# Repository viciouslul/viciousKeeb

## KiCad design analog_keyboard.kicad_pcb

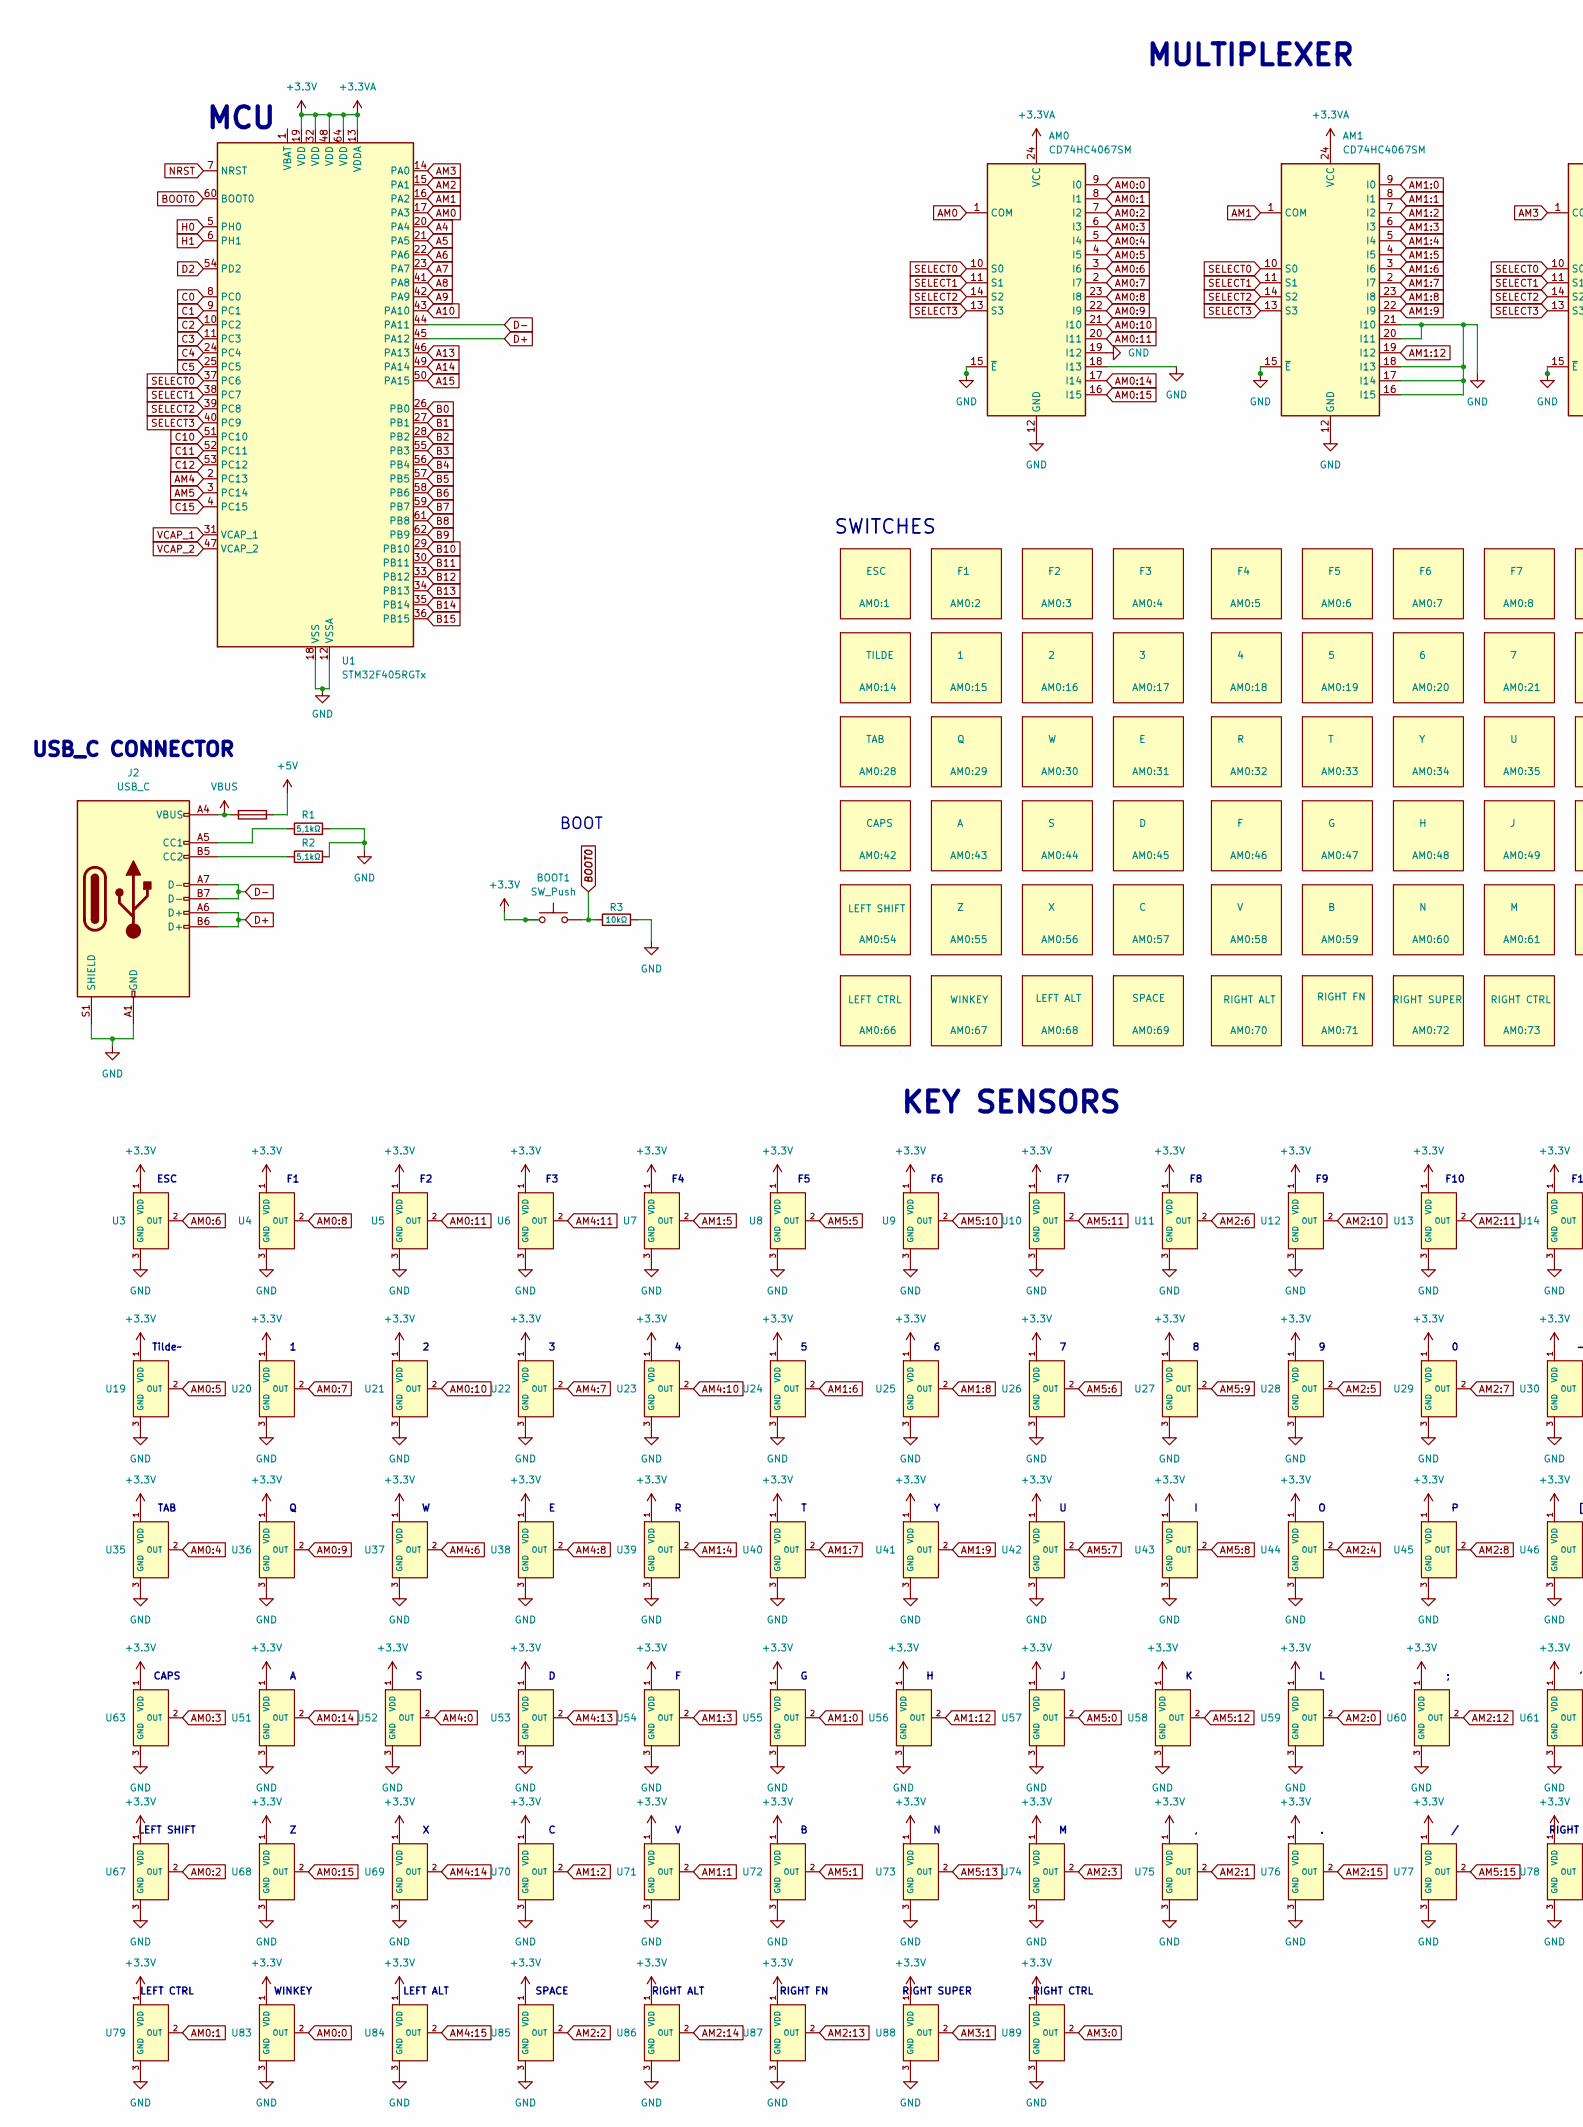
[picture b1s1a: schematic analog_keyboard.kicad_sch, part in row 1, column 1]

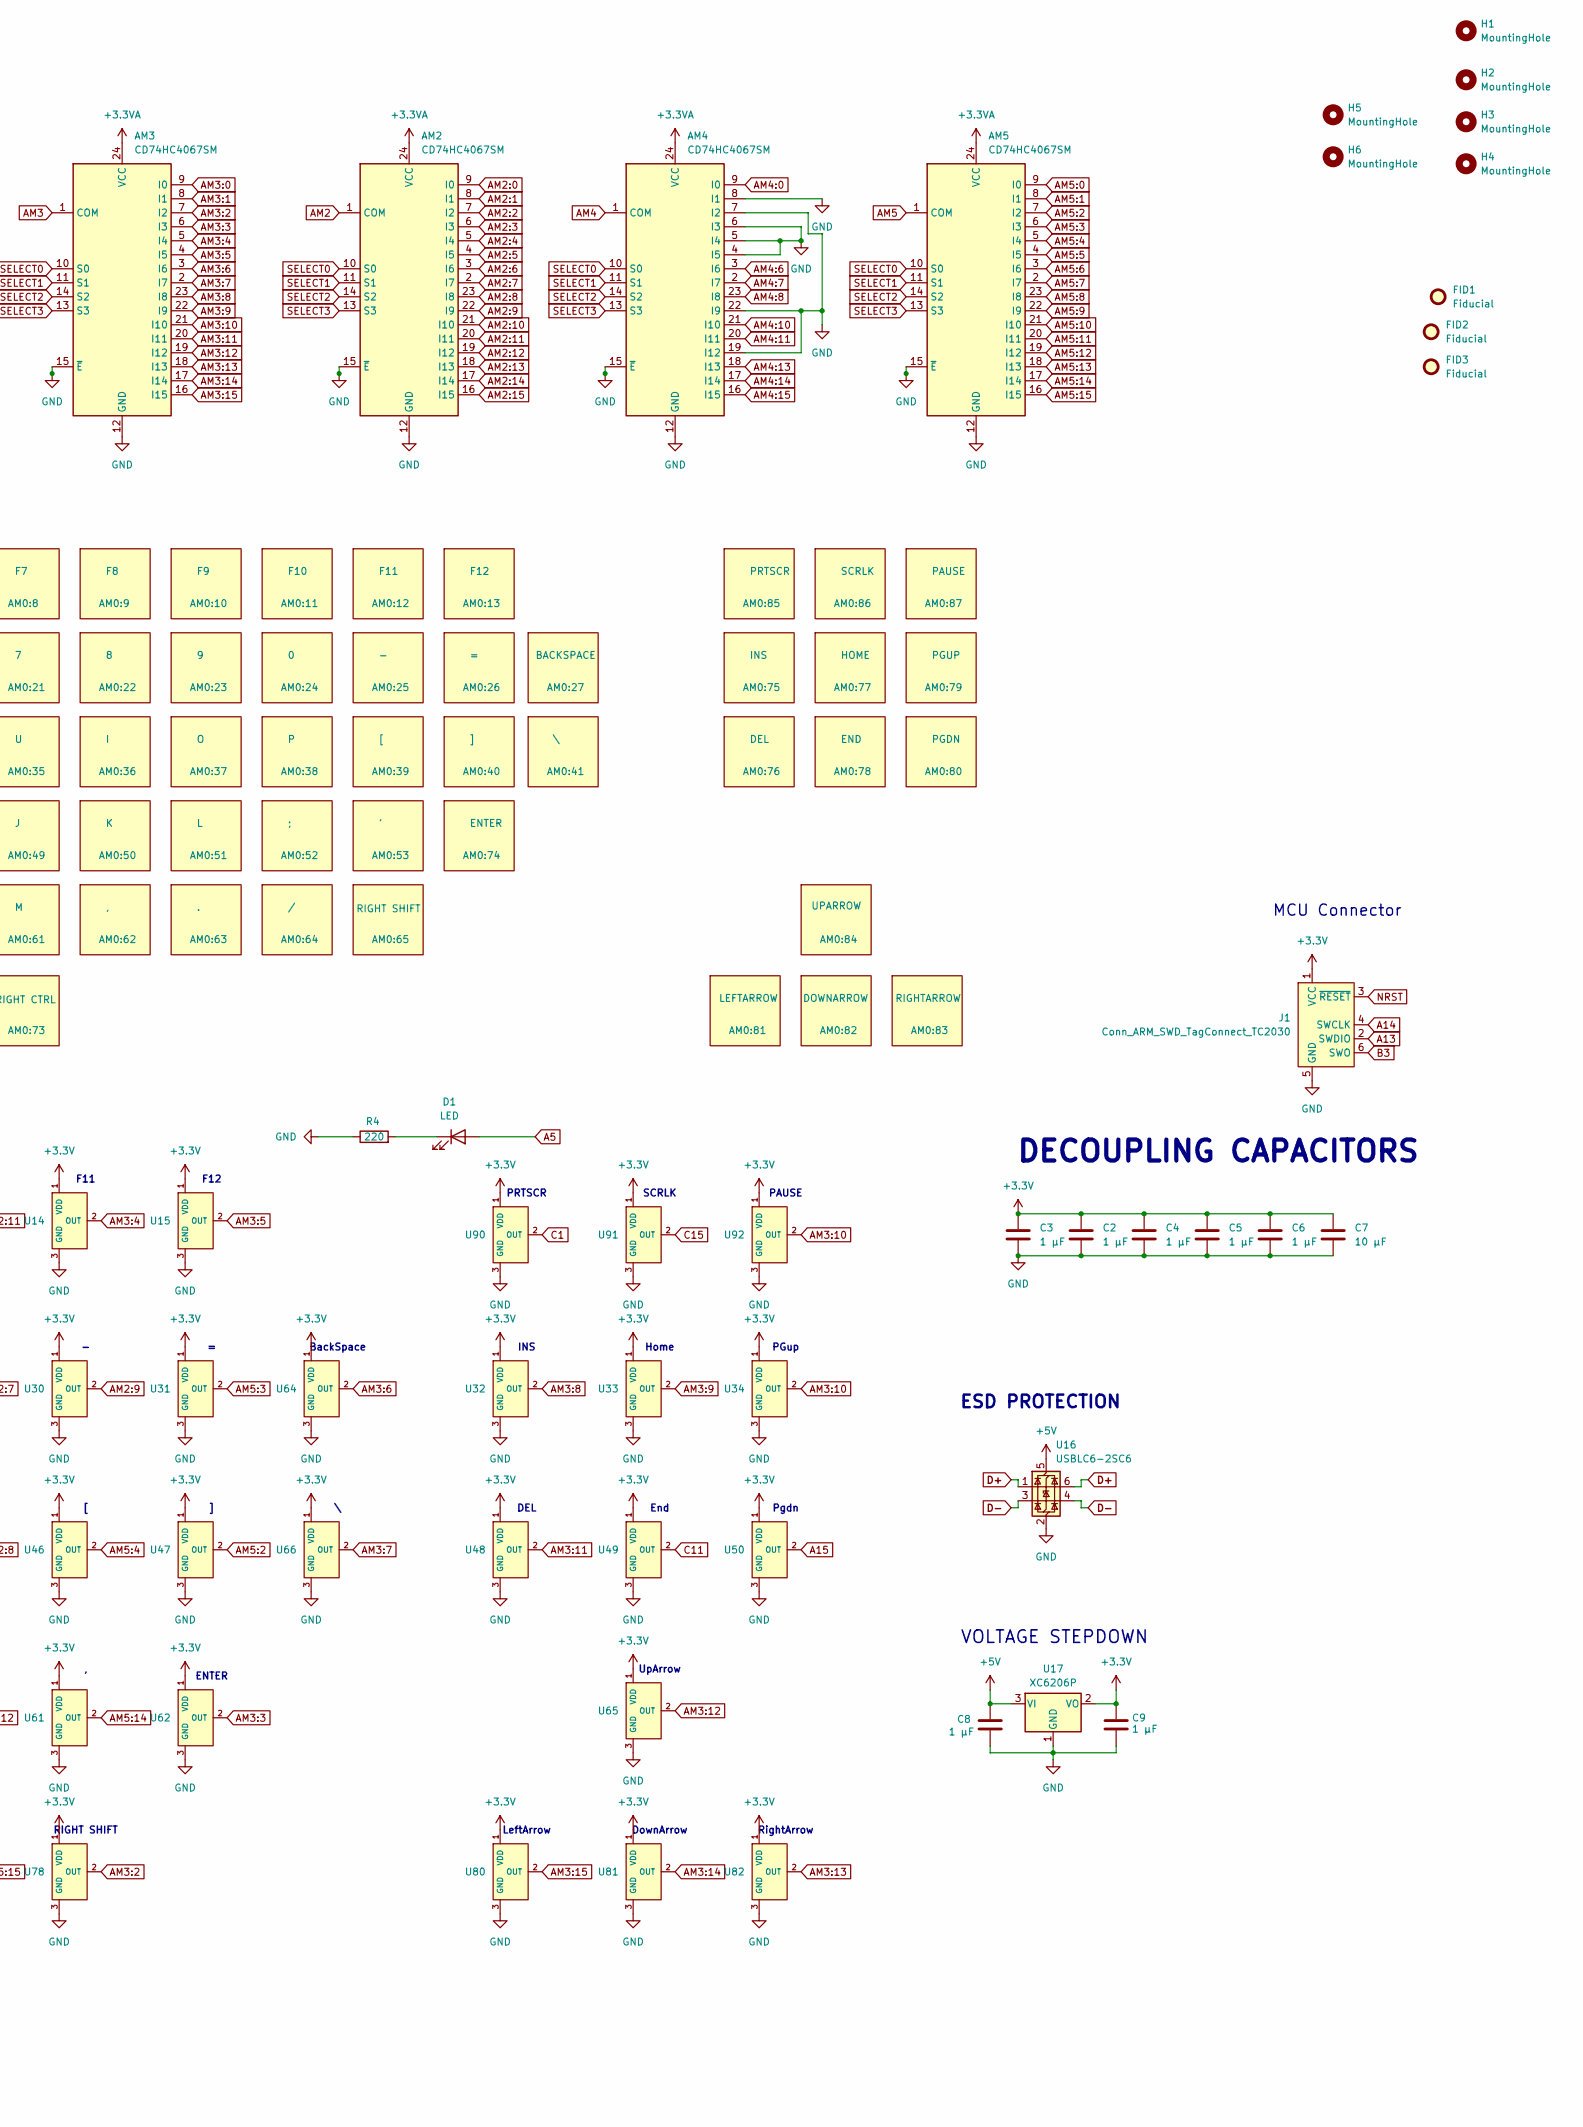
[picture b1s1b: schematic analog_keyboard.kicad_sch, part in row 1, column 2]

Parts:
AM0, AM1, AM2, AM3, AM4, AM5: CD74HC4067SM; SSOP-24_5.3x8.2mm_P0.65mm
AM0:1: ESC; HESwitch_1u_SMD
AM0:2: F1; HESwitch_1u_SMD
AM0:3: F2; HESwitch_1u_SMD
AM0:4: F3; HESwitch_1u_SMD
AM0:5: F4; HESwitch_1u_SMD
AM0:6: F5; HESwitch_1u_SMD
AM0:7: F6; HESwitch_1u_SMD
AM0:8: F7; HESwitch_1u_SMD
AM0:9: F8; HESwitch_1u_SMD
AM0:10: F9; HESwitch_1u_SMD
AM0:11: F10; HESwitch_1u_SMD
AM0:12: F11; HESwitch_1u_SMD
AM0:13: F12; HESwitch_1u_SMD
AM0:14: TILDE; HESwitch_1u_SMD
AM0:15: 1; HESwitch_1u_SMD
AM0:16: 2; HESwitch_1u_SMD
AM0:17: 3; HESwitch_1u_SMD
AM0:18: 4; HESwitch_1u_SMD
AM0:19: 5; HESwitch_1u_SMD
AM0:20: 6; HESwitch_1u_SMD
AM0:21: 7; HESwitch_1u_SMD
AM0:22: 8; HESwitch_1u_SMD
AM0:23: 9; HESwitch_1u_SMD
AM0:24: 0; HESwitch_1u_SMD
AM0:25: -; HESwitch_1u_SMD
AM0:26: =; HESwitch_1u_SMD
AM0:27: BACKSPACE; HESwitch_2u_SMD
AM0:28: TAB; HESwitch_1.5u_SMD
AM0:29: Q; HESwitch_1u_SMD
AM0:30: W; HESwitch_1u_SMD
AM0:31: E; HESwitch_1u_SMD
AM0:32: R; HESwitch_1u_SMD
AM0:33: T; HESwitch_1u_SMD
AM0:34: Y; HESwitch_1u_SMD
AM0:35: U; HESwitch_1u_SMD
AM0:36: I; HESwitch_1u_SMD
AM0:37: O; HESwitch_1u_SMD
AM0:38: P; HESwitch_1u_SMD
AM0:39: [; HESwitch_1u_SMD
AM0:40: ]; HESwitch_1u_SMD
AM0:41: \; HESwitch_1.5u_SMD
AM0:42: CAPS; HESwitch_1.75u_SMD
AM0:43: A; HESwitch_1u_SMD
AM0:44: S; HESwitch_1u_SMD
AM0:45: D; HESwitch_1u_SMD
AM0:46: F; HESwitch_1u_SMD
AM0:47: G; HESwitch_1u_SMD
AM0:48: H; HESwitch_1u_SMD
AM0:49: J; HESwitch_1u_SMD
AM0:50: K; HESwitch_1u_SMD
AM0:51: L; HESwitch_1u_SMD
AM0:52: ;; HESwitch_1u_SMD
AM0:53: '; HESwitch_1u_SMD
AM0:54: LEFT SHIFT; HESwitch_2.25u_SMD
AM0:55: Z; HESwitch_1u_SMD
AM0:56: X; HESwitch_1u_SMD
AM0:57: C; HESwitch_1u_SMD
AM0:58: V; HESwitch_1u_SMD
AM0:59: B; HESwitch_1u_SMD
AM0:60: N; HESwitch_1u_SMD
AM0:61: M; HESwitch_1u_SMD
AM0:62: ,; HESwitch_1u_SMD
AM0:63: .; HESwitch_1u_SMD
AM0:64: /; HESwitch_1u_SMD
AM0:65: RIGHT SHIFT; HESwitch_2.75u_SMD
AM0:66: LEFT CTRL; HESwitch_1.25u_SMD
AM0:67: WINKEY; HESwitch_1.25u_SMD
AM0:68: LEFT ALT; HESwitch_1.25u_SMD
AM0:69: SPACE; HESwitch_6.25u_SMD
AM0:70: RIGHT ALT; HESwitch_1.25u_SMD
AM0:71: RIGHT FN; HESwitch_1.25u_SMD
AM0:72: RIGHT SUPER; HESwitch_1.25u_SMD
AM0:73: RIGHT CTRL; HESwitch_1.25u_SMD
AM0:74: ENTER; HESwitch_2.25u_SMD
AM0:75: INS; HESwitch_1u_SMD
AM0:76: DEL; HESwitch_1u_SMD
AM0:77: HOME; HESwitch_1u_SMD
AM0:78: END; HESwitch_1u_SMD
AM0:79: PGUP; HESwitch_1u_SMD
AM0:80: PGDN; HESwitch_1u_SMD
AM0:81: LEFTARROW; HESwitch_1u_SMD
AM0:82: DOWNARROW; HESwitch_1u_SMD
AM0:83: RIGHTARROW; HESwitch_1u_SMD
AM0:84: UPARROW; HESwitch_1u_SMD
AM0:85: PRTSCR; HESwitch_1u_SMD
AM0:86: SCRLK; HESwitch_1u_SMD
AM0:87: PAUSE; HESwitch_1u_SMD
BOOT1: SW_Push; SW_SPST_TL3342
C2, C3, C4, C5, C6, C8, C9: 1 μF; C_0402_1005Metric
C7: 10 μF; C_0402_1005Metric
D1: LED; LED_0402_1005Metric
F1: 500mA; Fuse_1206_3216Metric
FID1, FID2, FID3: Fiducial; Fiducial_1mm_Mask2mm
H1, H2, H3, H4, H5, H6: MountingHole; MountingHole_2.2mm_M2_DIN965_Pad
J1: Conn_ARM_SWD_TagConnect_TC2030; Tag-Connect_TC2030-IDC-FP_2x03_P1.27mm_Vertical
J2: USB_C; USB_C_Receptacle_HRO_TYPE-C-31-M-12; LCSC Part C165948
R1, R2: 5,1kΩ; R_0402_1005Metric
R3: 10kΩ; R_0402_1005Metric
R4: 220; R_0402_1005Metric
U1: STM32F405RGTx; LQFP-64_10x10mm_P0.5mm
U2: (no value)
U3, U4, U5, U6, U7, U8, U9, U10, U11, U12, U13, U14, U15, U19, U20, U21, U22, U23, U24, U25, U26, U27, U28, U29, U30, U31, U32, U33, U34, U35, U36, U37, U38, U39, U40, U41, U42, U43, U44, U45, U46, U47, U48, U49, U50, U51, U52, U53, U54, U55, U56, U57, U58, U59, U60, U61, U62, U63, U64, U65, U66, U67, U68, U69, U70, U71, U72, U73, U74, U75, U76, U77, U78, U79, U80, U81, U82, U83, U84, U85, U86, U87, U88, U89, U90, U91, U92: Hall_Sensor; SOT-23; MPN GH39FKSW; LCSC Part C266230
U16: USBLC6-2SC6; SOT-23-6
U17: XC6206P; SOT-23-3

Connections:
+3.3V: AM0.24 (VCC), AM1.24 (VCC), AM2.24 (VCC), AM3.24 (VCC), AM4.24 (VCC), AM5.24 (VCC), BOOT1.1, C2.1, C3.1, C4.1, C5.1, C6.1, C7.1, C9.1, J1.1 (VCC), U1.13 (VDDA), U1.19 (VDD), U1.32 (VDD), U1.48 (VDD), U1.64 (VDD), U3.1 (VDD), U4.1 (VDD), U5.1 (VDD), U6.1 (VDD), U7.1 (VDD), U8.1 (VDD), U9.1 (VDD), U10.1 (VDD), U11.1 (VDD), U12.1 (VDD), U13.1 (VDD), U14.1 (VDD), U15.1 (VDD), U17.2 (VO), U19.1 (VDD), U20.1 (VDD), U21.1 (VDD), U22.1 (VDD), U23.1 (VDD), U24.1 (VDD), U25.1 (VDD), U26.1 (VDD), U27.1 (VDD), U28.1 (VDD), U29.1 (VDD), U30.1 (VDD), U31.1 (VDD), U32.1 (VDD), U33.1 (VDD), U34.1 (VDD), U35.1 (VDD), U36.1 (VDD), U37.1 (VDD), U38.1 (VDD), U39.1 (VDD), U40.1 (VDD), U41.1 (VDD), U42.1 (VDD), U43.1 (VDD), U44.1 (VDD), U45.1 (VDD), U46.1 (VDD), U47.1 (VDD), U48.1 (VDD), U49.1 (VDD), U50.1 (VDD), U51.1 (VDD), U52.1 (VDD), U53.1 (VDD), U54.1 (VDD), U55.1 (VDD), U56.1 (VDD), U57.1 (VDD), U58.1 (VDD), U59.1 (VDD), U60.1 (VDD), U61.1 (VDD), U62.1 (VDD), U63.1 (VDD), U64.1 (VDD), U65.1 (VDD), U66.1 (VDD), U67.1 (VDD), U68.1 (VDD), U69.1 (VDD), U70.1 (VDD), U71.1 (VDD), U72.1 (VDD), U73.1 (VDD), U74.1 (VDD), U75.1 (VDD), U76.1 (VDD), U77.1 (VDD), U78.1 (VDD), U79.1 (VDD), U80.1 (VDD), U81.1 (VDD), U82.1 (VDD), U83.1 (VDD), U84.1 (VDD), U85.1 (VDD), U86.1 (VDD), U87.1 (VDD), U88.1 (VDD), U89.1 (VDD), U90.1 (VDD), U91.1 (VDD), U92.1 (VDD)
+5V: C8.1, F1.1, U16.5 (VBUS), U17.3 (VI)
A4: U1.20 (PA4)
A5: D1.2 (A), U1.21 (PA5)
A6: U1.22 (PA6)
A7: U1.23 (PA7)
A8: U1.41 (PA8)
A9: U1.42 (PA9)
A10: U1.43 (PA10)
A13: J1.2 (SWDIO), U1.46 (PA13)
A14: J1.4 (SWCLK), U1.49 (PA14)
A15: U1.50 (PA15), U50.2 (OUT)
AM0: AM0.1 (COM), U1.17 (PA3)
AM0:0: AM0.9 (I0), U83.2 (OUT)
AM0:1: AM0.8 (I1), U79.2 (OUT)
AM0:2: AM0.7 (I2), U67.2 (OUT)
AM0:3: AM0.6 (I3), U63.2 (OUT)
AM0:4: AM0.5 (I4), U35.2 (OUT)
AM0:5: AM0.4 (I5), U19.2 (OUT)
AM0:6: AM0.3 (I6), U3.2 (OUT)
AM0:7: AM0.2 (I7), U20.2 (OUT)
AM0:8: AM0.23 (I8), U4.2 (OUT)
AM0:9: AM0.22 (I9), U36.2 (OUT)
AM0:10: AM0.21 (I10), U21.2 (OUT)
AM0:11: AM0.20 (I11), U5.2 (OUT)
AM0:14: AM0.17 (I14), U51.2 (OUT)
AM0:15: AM0.16 (I15), U68.2 (OUT)
AM1: AM1.1 (COM), U1.16 (PA2)
AM1:0: AM1.9 (I0), U55.2 (OUT)
AM1:1: AM1.8 (I1), U71.2 (OUT)
AM1:2: AM1.7 (I2), U70.2 (OUT)
AM1:3: AM1.6 (I3), U54.2 (OUT)
AM1:4: AM1.5 (I4), U39.2 (OUT)
AM1:5: AM1.4 (I5), U7.2 (OUT)
AM1:6: AM1.3 (I6), U24.2 (OUT)
AM1:7: AM1.2 (I7), U40.2 (OUT)
AM1:8: AM1.23 (I8), U25.2 (OUT)
AM1:9: AM1.22 (I9), U41.2 (OUT)
AM1:12: AM1.19 (I12), U56.2 (OUT)
AM2: AM2.1 (COM), U1.15 (PA1)
AM2:0: AM2.9 (I0), U59.2 (OUT)
AM2:1: AM2.8 (I1), U75.2 (OUT)
AM2:2: AM2.7 (I2), U85.2 (OUT)
AM2:3: AM2.6 (I3), U74.2 (OUT)
AM2:4: AM2.5 (I4), U44.2 (OUT)
AM2:5: AM2.4 (I5), U28.2 (OUT)
AM2:6: AM2.3 (I6), U11.2 (OUT)
AM2:7: AM2.2 (I7), U29.2 (OUT)
AM2:8: AM2.23 (I8), U45.2 (OUT)
AM2:9: AM2.22 (I9), U30.2 (OUT)
AM2:10: AM2.21 (I10), U12.2 (OUT)
AM2:11: AM2.20 (I11), U13.2 (OUT)
AM2:12: AM2.19 (I12), U60.2 (OUT)
AM2:13: AM2.18 (I13), U87.2 (OUT)
AM2:14: AM2.17 (I14), U86.2 (OUT)
AM2:15: AM2.16 (I15), U76.2 (OUT)
AM3: AM3.1 (COM), U1.14 (PA0)
AM3:0: AM3.9 (I0), U89.2 (OUT)
AM3:1: AM3.8 (I1), U88.2 (OUT)
AM3:2: AM3.7 (I2), U78.2 (OUT)
AM3:3: AM3.6 (I3), U62.2 (OUT)
AM3:4: AM3.5 (I4), U14.2 (OUT)
AM3:5: AM3.4 (I5), U15.2 (OUT)
AM3:6: AM3.3 (I6), U64.2 (OUT)
AM3:7: AM3.2 (I7), U66.2 (OUT)
AM3:8: AM3.23 (I8), U32.2 (OUT)
AM3:9: AM3.22 (I9), U33.2 (OUT)
AM3:11: AM3.20 (I11), U48.2 (OUT)
AM3:12: AM3.19 (I12), U65.2 (OUT)
AM3:13: AM3.18 (I13), U82.2 (OUT)
AM3:14: AM3.17 (I14), U81.2 (OUT)
AM3:15: AM3.16 (I15), U80.2 (OUT)
AM4: AM4.1 (COM), U1.2 (PC13)
AM4:0: AM4.9 (I0), U52.2 (OUT)
AM4:6: AM4.3 (I6), U37.2 (OUT)
AM4:7: AM4.2 (I7), U22.2 (OUT)
AM4:8: AM4.23 (I8), U38.2 (OUT)
AM4:10: AM4.21 (I10), U23.2 (OUT)
AM4:11: AM4.20 (I11), U6.2 (OUT)
AM4:13: AM4.18 (I13), U53.2 (OUT)
AM4:14: AM4.17 (I14), U69.2 (OUT)
AM4:15: AM4.16 (I15), U84.2 (OUT)
AM5: AM5.1 (COM), U1.3 (PC14)
AM5:0: AM5.9 (I0), U57.2 (OUT)
AM5:1: AM5.8 (I1), U72.2 (OUT)
AM5:2: AM5.7 (I2), U47.2 (OUT)
AM5:3: AM5.6 (I3), U31.2 (OUT)
AM5:4: AM5.5 (I4), U46.2 (OUT)
AM5:5: AM5.4 (I5), U8.2 (OUT)
AM5:6: AM5.3 (I6), U26.2 (OUT)
AM5:7: AM5.2 (I7), U42.2 (OUT)
AM5:8: AM5.23 (I8), U43.2 (OUT)
AM5:9: AM5.22 (I9), U27.2 (OUT)
AM5:10: AM5.21 (I10), U9.2 (OUT)
AM5:11: AM5.20 (I11), U10.2 (OUT)
AM5:12: AM5.19 (I12), U58.2 (OUT)
AM5:13: AM5.18 (I13), U73.2 (OUT)
AM5:14: AM5.17 (I14), U61.2 (OUT)
AM5:15: AM5.16 (I15), U77.2 (OUT)
B0: U1.26 (PB0)
B1: U1.27 (PB1)
B2: U1.28 (PB2)
B3: J1.6 (SWO), U1.55 (PB3)
B4: U1.56 (PB4)
B5: U1.57 (PB5)
B6: U1.58 (PB6)
B7: U1.59 (PB7)
B8: U1.61 (PB8)
B9: U1.62 (PB9)
B10: U1.29 (PB10)
B11: U1.30 (PB11)
B12: U1.33 (PB12)
B13: U1.34 (PB13)
B14: U1.35 (PB14)
B15: U1.36 (PB15)
BOOT0: BOOT1.2, R3.1, U1.60 (BOOT0)
C0: U1.8 (PC0)
C1: U1.9 (PC1), U90.2 (OUT)
C3: U1.11 (PC3)
C4: U1.24 (PC4)
C5: U1.25 (PC5)
C10: U1.51 (PC10)
C11: U1.52 (PC11), U49.2 (OUT)
C12: U1.53 (PC12)
C15: U1.4 (PC15), U91.2 (OUT)
D2: U1.54 (PD2)
D+: J2.A6 (D+), J2.B6 (D+), U1.45 (PA12), U16.1 (I/O1), U16.6 (I/O1)
D-: J2.A7 (D-), J2.B7 (D-), U1.44 (PA11), U16.3 (I/O2), U16.4 (I/O2)
GND: AM0.12 (GND), AM0.15 (~E), AM0.18 (I13), AM0.19 (I12), AM1.12 (GND), AM1.15 (~E), AM1.16 (I15), AM1.17 (I14), AM1.18 (I13), AM1.20 (I11), AM1.21 (I10), AM2.12 (GND), AM2.15 (~E), AM3.12 (GND), AM3.15 (~E), AM4.4 (I5), AM4.5 (I4), AM4.6 (I3), AM4.7 (I2), AM4.8 (I1), AM4.12 (GND), AM4.15 (~E), AM4.19 (I12), AM4.22 (I9), AM5.12 (GND), AM5.15 (~E), C2.2, C3.2, C4.2, C5.2, C6.2, C7.2, C8.2, C9.2, J1.5 (GND), J2.A1 (GND), J2.A12 (GND), J2.B1 (GND), J2.B12 (GND), J2.S1 (SHIELD), R1.2, R2.2, R3.2, R4.1, U1.12 (VSSA), U1.18 (VSS), U1.63 (VSS), U3.3 (GND), U4.3 (GND), U5.3 (GND), U6.3 (GND), U7.3 (GND), U8.3 (GND), U9.3 (GND), U10.3 (GND), U11.3 (GND), U12.3 (GND), U13.3 (GND), U14.3 (GND), U15.3 (GND), U16.2 (GND), U17.1 (GND), U19.3 (GND), U20.3 (GND), U21.3 (GND), U22.3 (GND), U23.3 (GND), U24.3 (GND), U25.3 (GND), U26.3 (GND), U27.3 (GND), U28.3 (GND), U29.3 (GND), U30.3 (GND), U31.3 (GND), U32.3 (GND), U33.3 (GND), U34.3 (GND), U35.3 (GND), U36.3 (GND), U37.3 (GND), U38.3 (GND), U39.3 (GND), U40.3 (GND), U41.3 (GND), U42.3 (GND), U43.3 (GND), U44.3 (GND), U45.3 (GND), U46.3 (GND), U47.3 (GND), U48.3 (GND), U49.3 (GND), U50.3 (GND), U51.3 (GND), U52.3 (GND), U53.3 (GND), U54.3 (GND), U55.3 (GND), U56.3 (GND), U57.3 (GND), U58.3 (GND), U59.3 (GND), U60.3 (GND), U61.3 (GND), U62.3 (GND), U63.3 (GND), U64.3 (GND), U65.3 (GND), U66.3 (GND), U67.3 (GND), U68.3 (GND), U69.3 (GND), U70.3 (GND), U71.3 (GND), U72.3 (GND), U73.3 (GND), U74.3 (GND), U75.3 (GND), U76.3 (GND), U77.3 (GND), U78.3 (GND), U79.3 (GND), U80.3 (GND), U81.3 (GND), U82.3 (GND), U83.3 (GND), U84.3 (GND), U85.3 (GND), U86.3 (GND), U87.3 (GND), U88.3 (GND), U89.3 (GND), U90.3 (GND), U91.3 (GND), U92.3 (GND)
H0: U1.5 (PH0)
H1: U1.6 (PH1)
NRST: J1.3 (~RESET), U1.7 (NRST)
unnamed: D1.1 (K), R4.2
unnamed: J2.A5 (CC1), R1.1
unnamed: J2.B5 (CC2), R2.1
SELECT0: AM0.10 (S0), AM1.10 (S0), AM2.10 (S0), AM3.10 (S0), AM4.10 (S0), AM5.10 (S0), U1.37 (PC6)
SELECT1: AM0.11 (S1), AM1.11 (S1), AM2.11 (S1), AM3.11 (S1), AM4.11 (S1), AM5.11 (S1), U1.38 (PC7)
SELECT2: AM0.14 (S2), AM1.14 (S2), AM2.14 (S2), AM3.14 (S2), AM4.14 (S2), AM5.14 (S2), U1.39 (PC8)
SELECT3: AM0.13 (S3), AM1.13 (S3), AM2.13 (S3), AM3.13 (S3), AM4.13 (S3), AM5.13 (S3), U1.40 (PC9)
VBUS: F1.2, J2.A4 (VBUS), J2.A9 (VBUS), J2.B4 (VBUS), J2.B9 (VBUS)
VCAP_1: U1.31 (VCAP_1)
VCAP_2: U1.47 (VCAP_2)

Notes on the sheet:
PAUSE
RightArrow
INS
RIGHT CTRL
Home
CAPS
RIGHT FN
MCU Connector
F12
Pgdn
TAB
LeftArrow
BackSpace
SPACE
End
LEFT CTRL
Tilde~
ESC
UpArrow
BOOT
VOLTAGE STEPDOWN
RIGHT ALT
WINKEY
SWITCHES
ENTER
KEY SENSORS
LEFT SHIFT
DEL
PRTSCR
ESD PROTECTION
DECOUPLING CAPACITORS
F11
LEFT ALT
USB_C CONNECTOR
RIGHT SUPER
DownArrow
SCRLK
MULTIPLEXER
MCU
RIGHT SHIFT

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
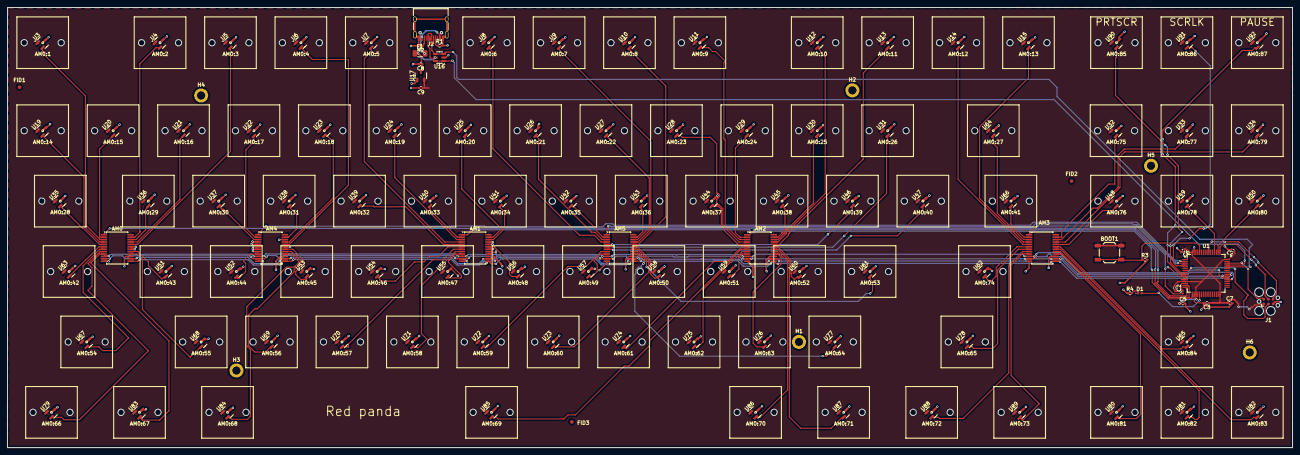
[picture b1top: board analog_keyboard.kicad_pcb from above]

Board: 2 copper layers, 347.7 x 119.1 mm, 209 parts (0 on the bottom side), 112 nets.

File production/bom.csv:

Designator,Footprint,Quantity,Value,LCSC Part #
"AM0,AM1,AM2,AM3,AM4,AM5",SSOP-24_5.3x8.2mm_P0.65mm,6,CD74HC4067SM,
BOOT1,SW_SPST_TL3342,1,SW_Push,
"C4,C8,C5,C2,C3,C9,C6",C_0402_1005Metric,7,1 μF,C14445,
C7,C_0402_1005Metric,1,10 μF,C315248,
D1,LED_0402_1005Metric,1,LED,C72038,
F1,Fuse_1206_3216Metric,1,500mA,C151133,
J2,USB_C_Receptacle_HRO_TYPE-C-31-M-12,1,USB_C,C165948,
"R1,R2",R_0402_1005Metric,2,5.1kΩ,C25905,
R3,R_0402_1005Metric,1,10kΩ,C60490,
R4,R_0402_1005Metric,1,220,
U1,LQFP-64_10x10mm_P0.5mm,1,STM32F405RGTx,
"U3,U4,U5,U6,U7,U8,U9,U10,U11,U12,U13,U14,U15,U19,U20,U21,U22,U23,U24,U25,U26,U27,U28,U29,U30,U31,U32,U33,U34,U35,U36,U37,U38,U39,U40,U41,U42,U43,U44,U45,U46,U47,U48,U49,U50,U51,U52,U53,U54,U55,U56,U57,U58,U59,U60,U61,U62,U63,U64,U65,U66,U67,U68,U69,U70,U71,U72,U73,U74,U75,U76,U77,U78,U79,U80,U81,U82,U83,U84,U85,U86,U87,U88,U89,U90,U91,U92",SOT-23,87,Hall_Sensor,C266230
U16,SOT-23-6,1,USBLC6-2SC6,C2827654,
U17,SOT-23-3,1,XC6206P,XC6206P332MR,
